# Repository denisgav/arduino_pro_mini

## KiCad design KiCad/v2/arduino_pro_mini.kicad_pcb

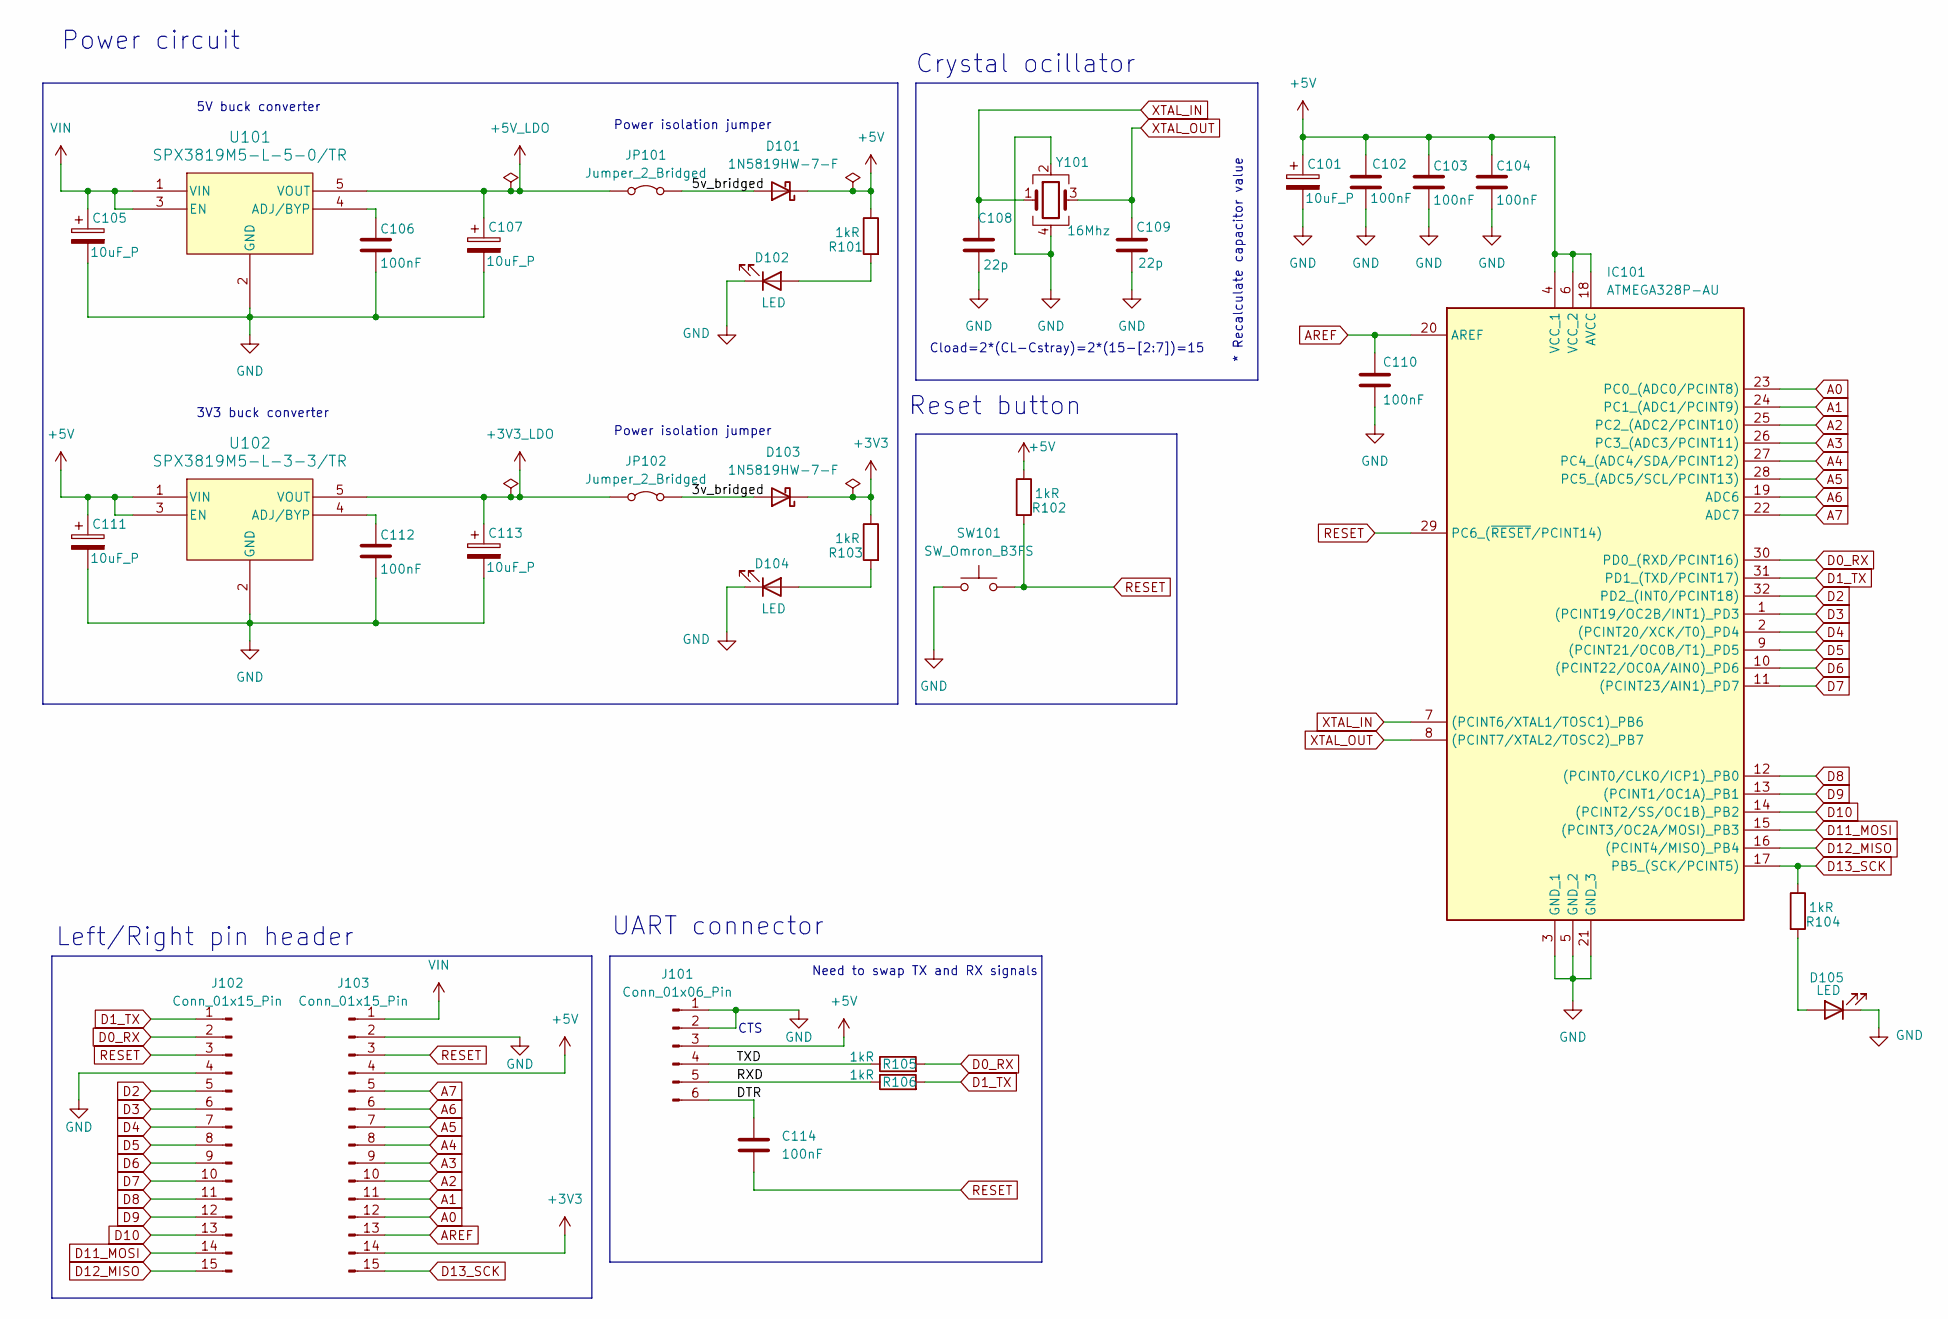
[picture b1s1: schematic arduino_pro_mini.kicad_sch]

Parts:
C101, C105, C107, C111, C113: 10uF_P; CP_EIA-3216-18_Kemet-A; Manufacturer Part Number TAJA106K016RNJ
C102, C103, C104, C106, C110, C112, C114: 100nF; C_0805_2012Metric; Manufacturer Part Number CC0805KRX7R9BB104
C108, C109: 22p; C_0603_1608Metric; Manufacturer Part Number CC0603JRNPO9BN220
D101, D103: 1N5819HW-7-F; D_SOD-123; Manufacturer Part Number 1N5819HW-7-F
D102, D104, D105: LED; LED_0603_1608Metric; Manufacturer Part Number XL-1608SURC-06
IC101: ATMEGA328P-AU; QFP80P900X900X120-32N; Manufacturer Part Number ATMEGA328P-AU
J101: Conn_01x06_Pin; PinHeader_1x06_P2.54mm_Vertical
J102, J103: Conn_01x15_Pin; PinHeader_1x15_P2.54mm_Vertical
JP101, JP102: Jumper_2_Bridged; TestPoint_2Pads_Pitch2.54mm_Drill0.8mm
R101, R102, R103, R104, R105, R106: 1kR; R_0603_1608Metric; Manufacturer Part Number RC0603FR-071KL
SW101: SW_Omron_B3FS; SW_SPST_Omron_B3FS-100xP; Manufacturer Part Number TSA063G50-250
U101: SPX3819M5-L-5-0/TR; SPX3819M5-L-TR
U102: SPX3819M5-L-3-3/TR; SPX3819M5-L-TR
Y101: 16Mhz; Crystal_SMD_3225-4Pin_3.2x2.5mm; Manufacturer Part Number X322516MRB4SI

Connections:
+3V3: D103.1 (K), J103.14, R103.1
+3V3_LDO: C113.1, JP102.1 (A), U102.5 (VOUT)
+5V: C101.1, C102.1, C103.1, C104.1, C111.1, D101.1 (K), IC101.4 (VCC_1), IC101.6 (VCC_2), IC101.18 (AVCC), J101.3, J103.4, R101.1, R102.1, U102.1 (VIN), U102.3 (EN)
+5V_LDO: C107.1, JP101.1 (A), U101.5 (VOUT)
/3v_bridged: D103.2 (A), JP102.2 (B)
/5v_bridged: D101.2 (A), JP101.2 (B)
/DTR: C114.1, J101.6
/RXD: J101.5, R106.1
/TXD: J101.4, R105.1
A0: IC101.23 (PC0_(ADC0/PCINT8)), J103.12
A1: IC101.24 (PC1_(ADC1/PCINT9)), J103.11
A2: IC101.25 (PC2_(ADC2/PCINT10)), J103.10
A3: IC101.26 (PC3_(ADC3/PCINT11)), J103.9
A4: IC101.27 (PC4_(ADC4/SDA/PCINT12)), J103.8
A5: IC101.28 (PC5_(ADC5/SCL/PCINT13)), J103.7
A6: IC101.19 (ADC6), J103.6
A7: IC101.22 (ADC7), J103.5
AREF: C110.1, IC101.20 (AREF), J103.13
D0_RX: IC101.30 (PD0_(RXD/PCINT16)), J102.2, R105.2
D1_TX: IC101.31 (PD1_(TXD/PCINT17)), J102.1, R106.2
D2: IC101.32 (PD2_(INT0/PCINT18)), J102.5
D3: IC101.1 ((PCINT19/OC2B/INT1)_PD3), J102.6
D4: IC101.2 ((PCINT20/XCK/T0)_PD4), J102.7
D5: IC101.9 ((PCINT21/OC0B/T1)_PD5), J102.8
D6: IC101.10 ((PCINT22/OC0A/AIN0)_PD6), J102.9
D7: IC101.11 ((PCINT23/AIN1)_PD7), J102.10
D8: IC101.12 ((PCINT0/CLKO/ICP1)_PB0), J102.11
D9: IC101.13 ((PCINT1/OC1A)_PB1), J102.12
D10: IC101.14 ((PCINT2/SS/OC1B)_PB2), J102.13
D11_MOSI: IC101.15 ((PCINT3/OC2A/MOSI)_PB3), J102.14
D12_MISO: IC101.16 ((PCINT4/MISO)_PB4), J102.15
D13_SCK: IC101.17 (PB5_(SCK/PCINT5)), J103.15, R104.1
GND: C101.2, C102.2, C103.2, C104.2, C105.2, C106.2, C107.2, C108.2, C109.2, C110.2, C111.2, C112.2, C113.2, D102.1 (K), D104.1 (K), D105.1 (K), IC101.3 (GND_1), IC101.5 (GND_2), IC101.21 (GND_3), J101.1, J101.2, J102.4, J103.2, SW101.1, U101.2 (GND), U102.2 (GND), Y101.2, Y101.4
unnamed: D102.2 (A), R101.2
unnamed: D104.2 (A), R103.2
unnamed: D105.2 (A), R104.2
unnamed: C106.1, U101.4 (ADJ/BYP)
unnamed: C112.1, U102.4 (ADJ/BYP)
RESET: C114.2, IC101.29 (PC6_(~RESET/PCINT14)), J102.3, J103.3, R102.2, SW101.2
VIN: C105.1, J103.1, U101.1 (VIN), U101.3 (EN)
XTAL_IN: C108.1, IC101.7 ((PCINT6/XTAL1/TOSC1)_PB6), Y101.1
XTAL_OUT: C109.1, IC101.8 ((PCINT7/XTAL2/TOSC2)_PB7), Y101.3

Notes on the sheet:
Power isolation jumper
* Recalculate capacitor value
3V3 buck converter
UART connector
Need to swap TX and RX signals
5V buck converter
Reset button
Power circuit
Left/Right pin header
CTS
Cload=2*(CL-Cstray)=2*(15-[2:7])=15
Crystal ocillator

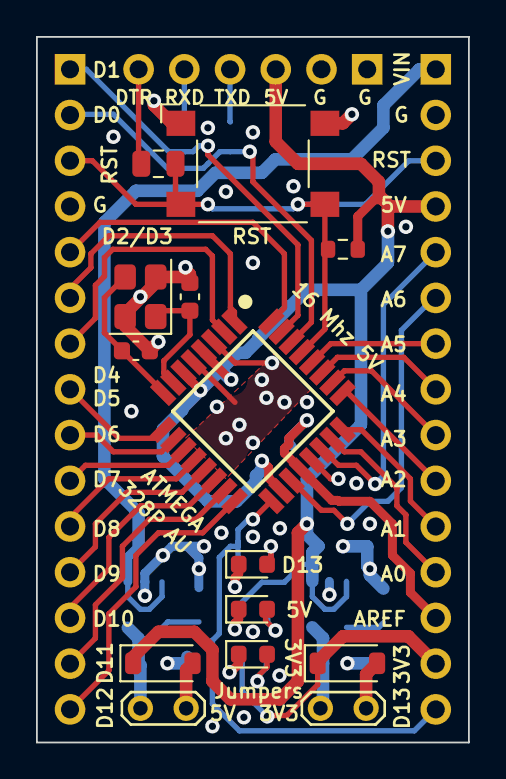
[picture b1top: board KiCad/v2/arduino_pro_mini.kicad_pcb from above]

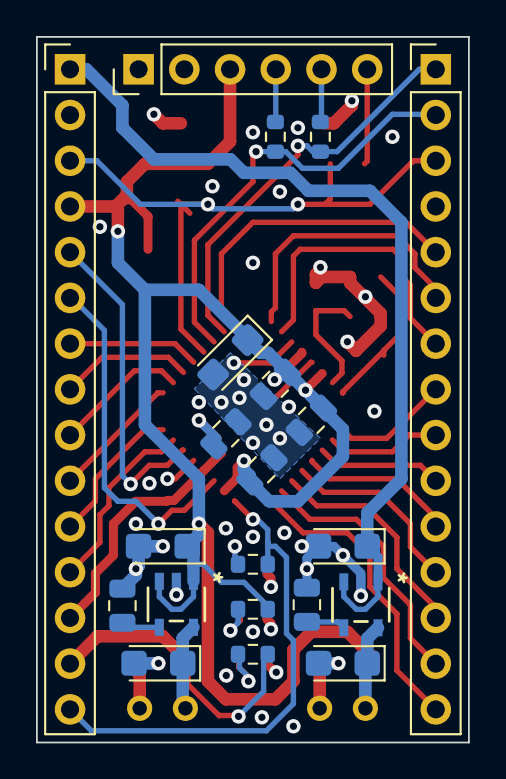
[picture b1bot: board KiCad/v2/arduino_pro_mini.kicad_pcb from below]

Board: 4 copper layers, 24.0 x 39.2 mm, 35 parts (21 on the bottom side), 42 nets.

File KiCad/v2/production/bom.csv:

Designator,Footprint,Quantity,Value,LCSC Part #
"C101, C105, C107, C111, C113",CP_EIA-3216-18_Kemet-A,5,10uF_P,
"C102, C103, C104, C106, C110, C112, C114",0805,7,100nF,
"C108, C109",0603,2,15p,
"D101, D103",D_SOD-123,2,1N5819HW-7-F,
"D102, D104, D105",0603,3,LED,
IC101,QFP80P900X900X120-32N,1,ATMEGA328P-AU,
J101,PinHeader_1x06_P2.54mm_Vertical,1,Conn_01x06_Pin,
"J102, J103",PinHeader_1x15_P2.54mm_Vertical,2,Conn_01x15_Pin,
"JP101, JP102",TestPoint_2Pads_Pitch2.54mm_Drill0.8mm,2,Jumper_2_Bridged,
"R101, R102, R103, R104, R105, R106",0603,6,1kR,
SW101,SW_SPST_Omron_B3FS-100xP,1,SW_Omron_B3FS,
U101,SPX3819M5-L-TR,1,SPX3819M5-L-5-0/TR,
U102,SPX3819M5-L-TR,1,SPX3819M5-L-3-3/TR,
Y101,Crystal_SMD_3225-4Pin_3.2x2.5mm,1,16Mhz,

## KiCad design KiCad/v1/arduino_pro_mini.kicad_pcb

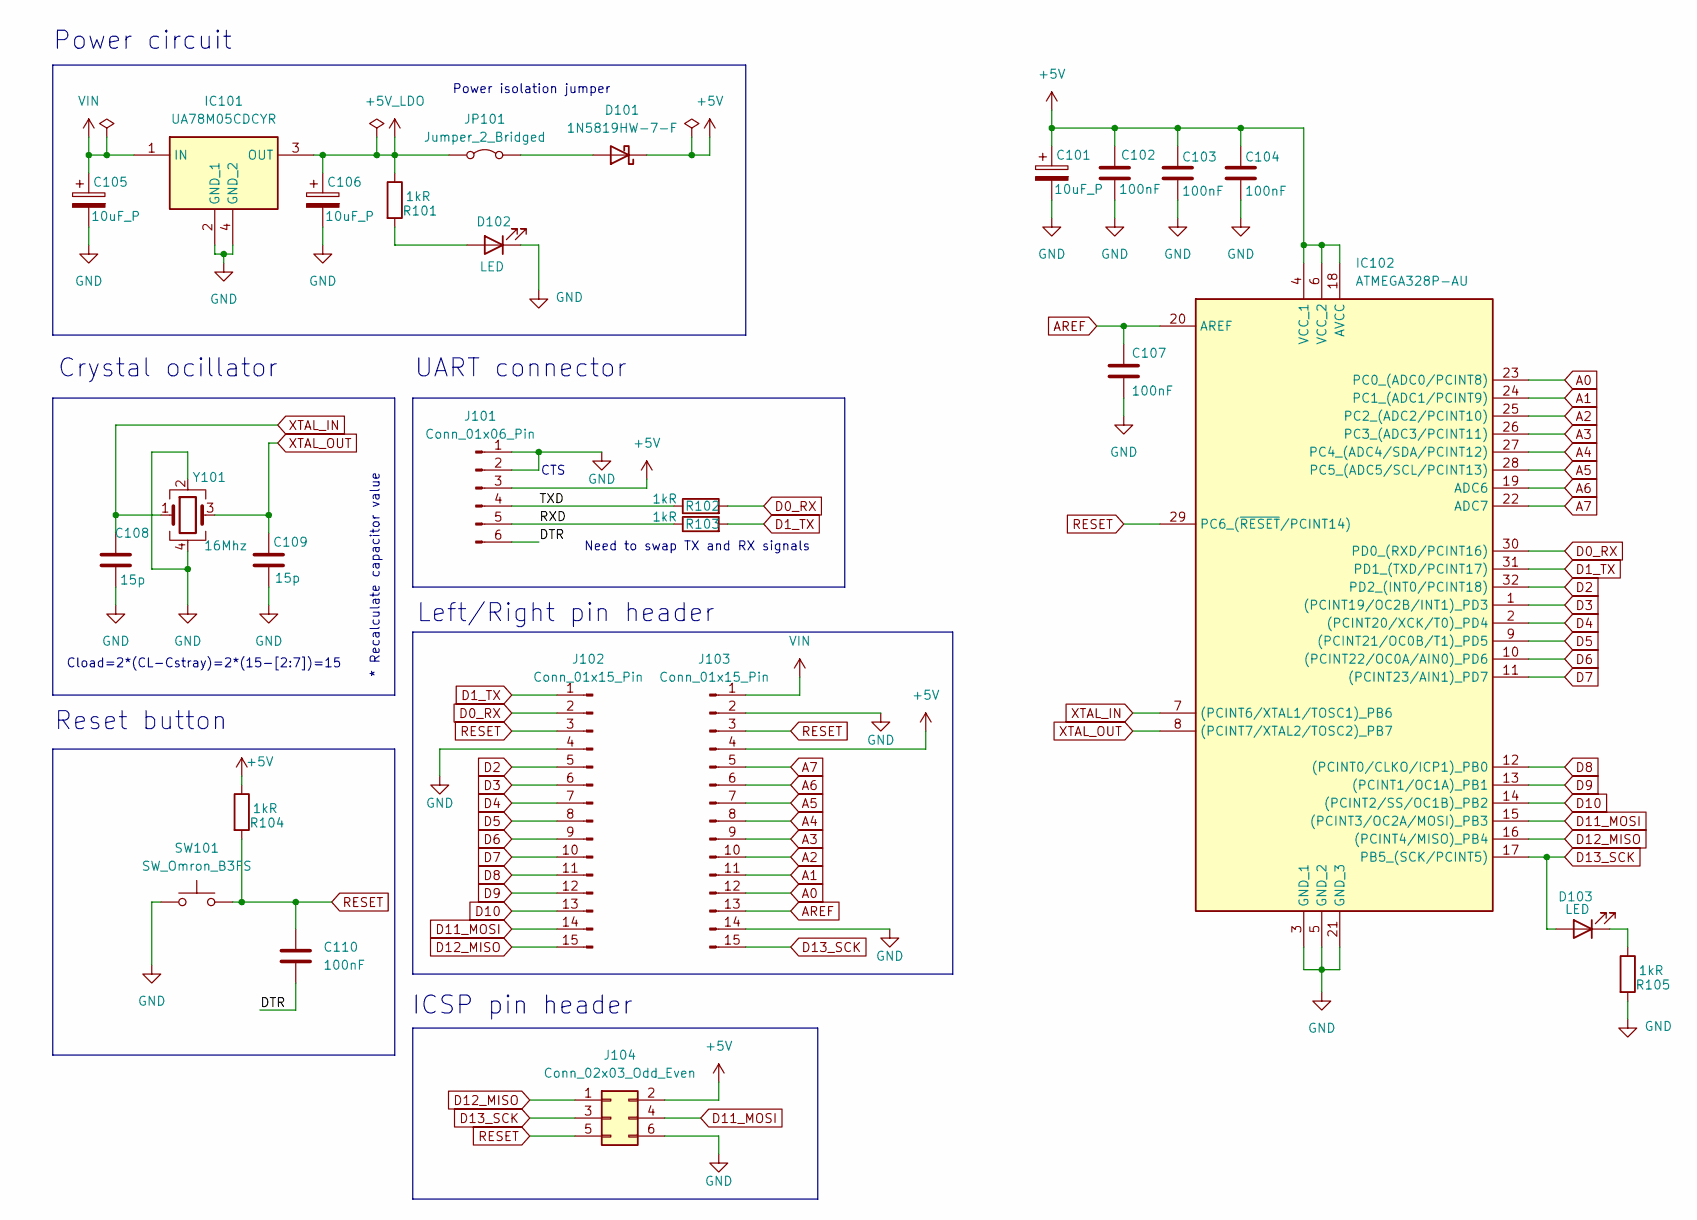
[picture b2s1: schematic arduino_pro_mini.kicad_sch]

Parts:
C101, C105, C106: 10uF_P; CP_EIA-3216-18_Kemet-A; Manufacturer Part Number TAJA106K016RNJ
C102, C103, C104, C107, C110: 100nF; C_0805_2012Metric; Manufacturer Part Number CC0805KRX7R9BB104
C108, C109: 15p; C_0603_1608Metric; Manufacturer Part Number CC0603JRNPO9BN150
D101: 1N5819HW-7-F; D_SOD-123; Manufacturer Part Number 1N5819HW-7-F
D102, D103: LED; LED_0603_1608Metric; Manufacturer Part Number XL-1608SURC-06
IC101: UA78M05CDCYR; SOT230P700X180-4N; Manufacturer Part Number UA78M05CDCYR
IC102: ATMEGA328P-AU; QFP80P900X900X120-32N; Manufacturer Part Number ATMEGA328P-AU
J101: Conn_01x06_Pin; PinHeader_1x06_P2.54mm_Vertical
J102, J103: Conn_01x15_Pin; PinHeader_1x15_P2.54mm_Vertical
J104: Conn_02x03_Odd_Even; PinHeader_2x03_P2.54mm_Vertical
JP101: Jumper_2_Bridged; TestPoint_2Pads_Pitch2.54mm_Drill0.8mm
R101, R102, R103, R104, R105: 1kR; R_0603_1608Metric; Manufacturer Part Number RC0603FR-071KL
SW101: SW_Omron_B3FS; SW_SPST_Omron_B3FS-100xP; Manufacturer Part Number TSA063G50-250
Y101: 16Mhz; Crystal_SMD_3225-4Pin_3.2x2.5mm; Manufacturer Part Number X322516MOB4SI

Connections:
+5V: C101.1, C102.1, C103.1, C104.1, D101.1 (K), IC102.4 (VCC_1), IC102.6 (VCC_2), IC102.18 (AVCC), J101.3, J103.4, J104.2, R104.1
+5V_LDO: C106.1, IC101.3 (OUT), JP101.1 (A), R101.1
/DTR: C110.2, J101.6
/RXD: J101.5, R103.1
/TXD: J101.4, R102.1
A0: IC102.23 (PC0_(ADC0/PCINT8)), J103.12
A1: IC102.24 (PC1_(ADC1/PCINT9)), J103.11
A2: IC102.25 (PC2_(ADC2/PCINT10)), J103.10
A3: IC102.26 (PC3_(ADC3/PCINT11)), J103.9
A4: IC102.27 (PC4_(ADC4/SDA/PCINT12)), J103.8
A5: IC102.28 (PC5_(ADC5/SCL/PCINT13)), J103.7
A6: IC102.19 (ADC6), J103.6
A7: IC102.22 (ADC7), J103.5
AREF: C107.1, IC102.20 (AREF), J103.13
D0_RX: IC102.30 (PD0_(RXD/PCINT16)), J102.2, R102.2
D1_TX: IC102.31 (PD1_(TXD/PCINT17)), J102.1, R103.2
D2: IC102.32 (PD2_(INT0/PCINT18)), J102.5
D3: IC102.1 ((PCINT19/OC2B/INT1)_PD3), J102.6
D4: IC102.2 ((PCINT20/XCK/T0)_PD4), J102.7
D5: IC102.9 ((PCINT21/OC0B/T1)_PD5), J102.8
D6: IC102.10 ((PCINT22/OC0A/AIN0)_PD6), J102.9
D7: IC102.11 ((PCINT23/AIN1)_PD7), J102.10
D8: IC102.12 ((PCINT0/CLKO/ICP1)_PB0), J102.11
D9: IC102.13 ((PCINT1/OC1A)_PB1), J102.12
D10: IC102.14 ((PCINT2/SS/OC1B)_PB2), J102.13
D11_MOSI: IC102.15 ((PCINT3/OC2A/MOSI)_PB3), J102.14, J104.4
D12_MISO: IC102.16 ((PCINT4/MISO)_PB4), J102.15, J104.1
D13_SCK: D103.2 (A), IC102.17 (PB5_(SCK/PCINT5)), J103.15, J104.3
GND: C101.2, C102.2, C103.2, C104.2, C105.2, C106.2, C107.2, C108.2, C109.2, D102.1 (K), IC101.2 (GND_1), IC101.4 (GND_2), IC102.3 (GND_1), IC102.5 (GND_2), IC102.21 (GND_3), J101.1, J101.2, J102.4, J103.2, J103.14, J104.6, R105.2, SW101.1, Y101.2, Y101.4
unnamed: D101.2 (A), JP101.2 (B)
unnamed: D102.2 (A), R101.2
unnamed: D103.1 (K), R105.1
RESET: C110.1, IC102.29 (PC6_(~RESET/PCINT14)), J102.3, J103.3, J104.5, R104.2, SW101.2
VIN: C105.1, IC101.1 (IN), J103.1
XTAL_IN: C108.1, IC102.7 ((PCINT6/XTAL1/TOSC1)_PB6), Y101.1
XTAL_OUT: C109.1, IC102.8 ((PCINT7/XTAL2/TOSC2)_PB7), Y101.3

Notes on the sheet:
* Recalculate capacitor value
ICSP pin header
UART connector
Need to swap TX and RX signals
Reset button
Power circuit
Left/Right pin header
CTS
Power isolation jumper
Cload=2*(CL-Cstray)=2*(15-[2:7])=15
Crystal ocillator

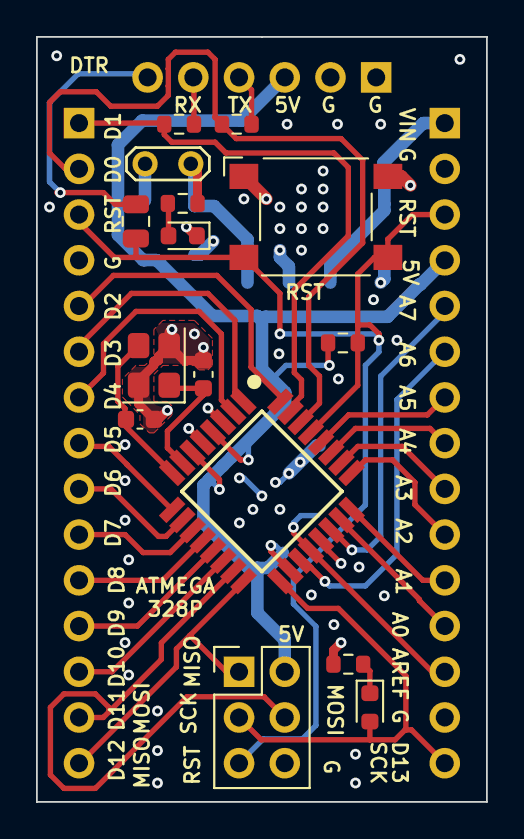
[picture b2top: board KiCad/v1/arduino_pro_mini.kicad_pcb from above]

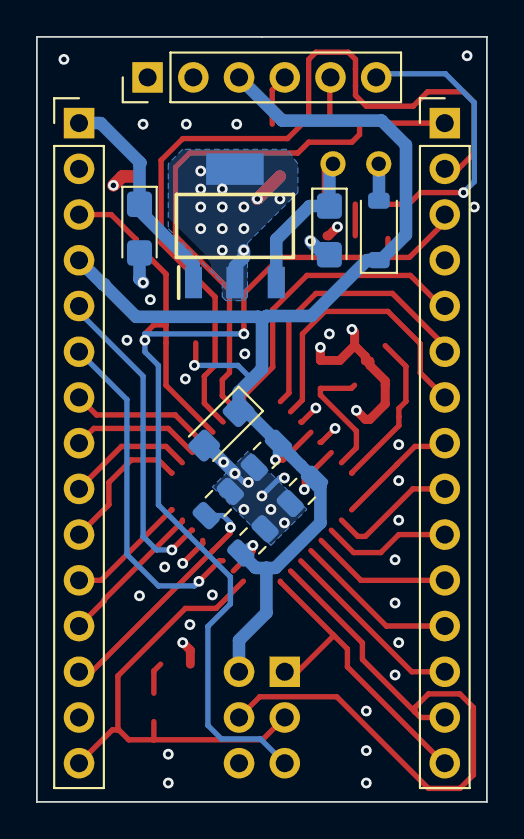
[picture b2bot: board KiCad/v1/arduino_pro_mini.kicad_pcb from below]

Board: 4 copper layers, 25.0 x 42.5 mm, 27 parts (12 on the bottom side), 36 nets.

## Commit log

2026-02-05 Add pushbutton
2026-02-06 Initial scheme
2026-02-06 first pcb component placement
2026-02-06 Board outline
2026-02-06 Add signal traces to PCB
2026-02-06 All connected
2026-02-06 silk screen updates
2026-02-06 UART signals routing update
2026-02-21 Add doc pdf
2026-02-28 Update BOM
2026-03-07 Update LDO
2026-03-07 Initial signal routing
2026-03-07 Power signals routing
2026-03-07 sulk screen updates
2026-03-07 DCR fix
2026-03-08 Update crystal oscillator
2026-03-09 JLCPCB rule check
2026-03-09 JLCPCB Checks
2026-03-09 Reset drill origin, grid origin
